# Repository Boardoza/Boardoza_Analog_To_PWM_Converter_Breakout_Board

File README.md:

# Boardoza Analog To PWM Converter Breakout Board

The **Boardoza Analog to PWM Converter Breakout Board** is a high-precision signal conditioning board designed to convert an analog voltage input into a proportional **PWM (Pulse Width Modulation)** output signal where the **duty cycle increases or decreases proportionally with the applied input voltage**. Built using high-speed operational amplifiers and comparators, this board operates entirely through dedicated hardware circuitry, enabling ultra-fast response times and reliable signal conversion without requiring any firmware or software processing.

This breakout board is ideal for **motor control systems, throttle signal conversion, industrial automation, power electronics, robotics, and embedded analog control applications**. Its low-latency architecture and robust analog signal path make it suitable for safety-critical and noise-sensitive environments where deterministic signal behavior is essential.

## [Click here to purchase!](https://www.ozdisan.com/ureticiler/boardoza)

|Front Side|Back Side|
|:---:|:---:|
| | |

---

## Key Features

- **Hardware-Based PWM Generation:** Converts analog voltage signals directly into PWM output without requiring a microcontroller.
- **Discrete Analog Design:** Built using precision operational amplifiers and comparators for stable and deterministic operation.
- **Low Latency Signal Path:** Near-instantaneous analog-to-PWM conversion suitable for real-time control systems.
- **Push-Pull CMOS Output:** Provides strong and clean logic-level PWM output compatible with many digital systems.
- **High Noise Immunity:** Reliable operation in electrically noisy environments such as motor drivers and industrial systems.

---

## Technical Specifications

**Model:** Analog to PWM Converter  
**Manufacturer:** Boardoza   
**Manufacturer IC:** Texas Instruments   
**Operational Amplifier Model:** OPA2356  
**Board Type:** Analog Signal Converter    
**Input Voltage (VCC):** 2.7V – 5.5V  
**Analog Input Range:** 0.1V – 4.9V  
**Output Type:** 20kHz PWM (Push-Pull CMOS Logic)  
**Comparator Type:** High-Speed Comparator with Integrated Reference  
**Operational Amplifier Type:** Rail-to-Rail High-Speed Op-Amp  
**Output Short Circuit Current:** 74mA  
**Operating Temperature:** -40°C to +125°C  
**Board Dimensions:** 40mm x 20mm  v

---

## Simulation and Test Results

Simulation and test results are provided below.

| Triangle Wave Output | Error Amplifier Output | PWM Output |
|:---:|:---:|:---:|
|  |  |  |

| Input 100mV | Input 3.3V |
|:---:|:---:|
|  |  |

---

## Board Pinout

### ( J1 ) Power & Analog Input Connector

| Pin Number | Pin Name | Description |
|:---:|:---:|---|
| 1 | VCC | Power Supply Input |
| 2 | INPUT | Analog Voltage Input / Throttle Signal |
| 3 | GND | Ground |

### ( J2 ) PWM Output Connector

| Pin Number | Pin Name | Description |
|:---:|:---:|---|
| 1 | VCC | Power Supply Input |
| 2 | GND | Ground |

---

## Board Dimensions

---

## Step Files

[Boardoza ANALOG to PWM Converter.step](./assets/ANALOG_To_PWM_Converter%20Step.step)

---

## Datasheet

[OPA2356 Datasheet.pdf](./assets/OPA2356xxD%20Datasheet.pdf)

[TLV3052 Datasheet.pdf](./assets/TLV3052AID%20Datasheet.pdf)

---

## Version History

- V1.0.0 - Initial Release

---

## Support

- If you have any questions or need support, please contact support@boardoza.com

---

## **License**
### **Hardware Design**

[![CC BY-SA 4.0][cc-by-sa-shield]][cc-by-sa]

All hardware design files are licensed under [Creative Commons Attribution-ShareAlike 4.0 International License][cc-by-sa].

[cc-by-sa]: http://creativecommons.org/licenses/by-sa/4.0/
[cc-by-sa-shield]: https://img.shields.io/badge/License-CC%20BY--SA%204.0-lightgrey.svg

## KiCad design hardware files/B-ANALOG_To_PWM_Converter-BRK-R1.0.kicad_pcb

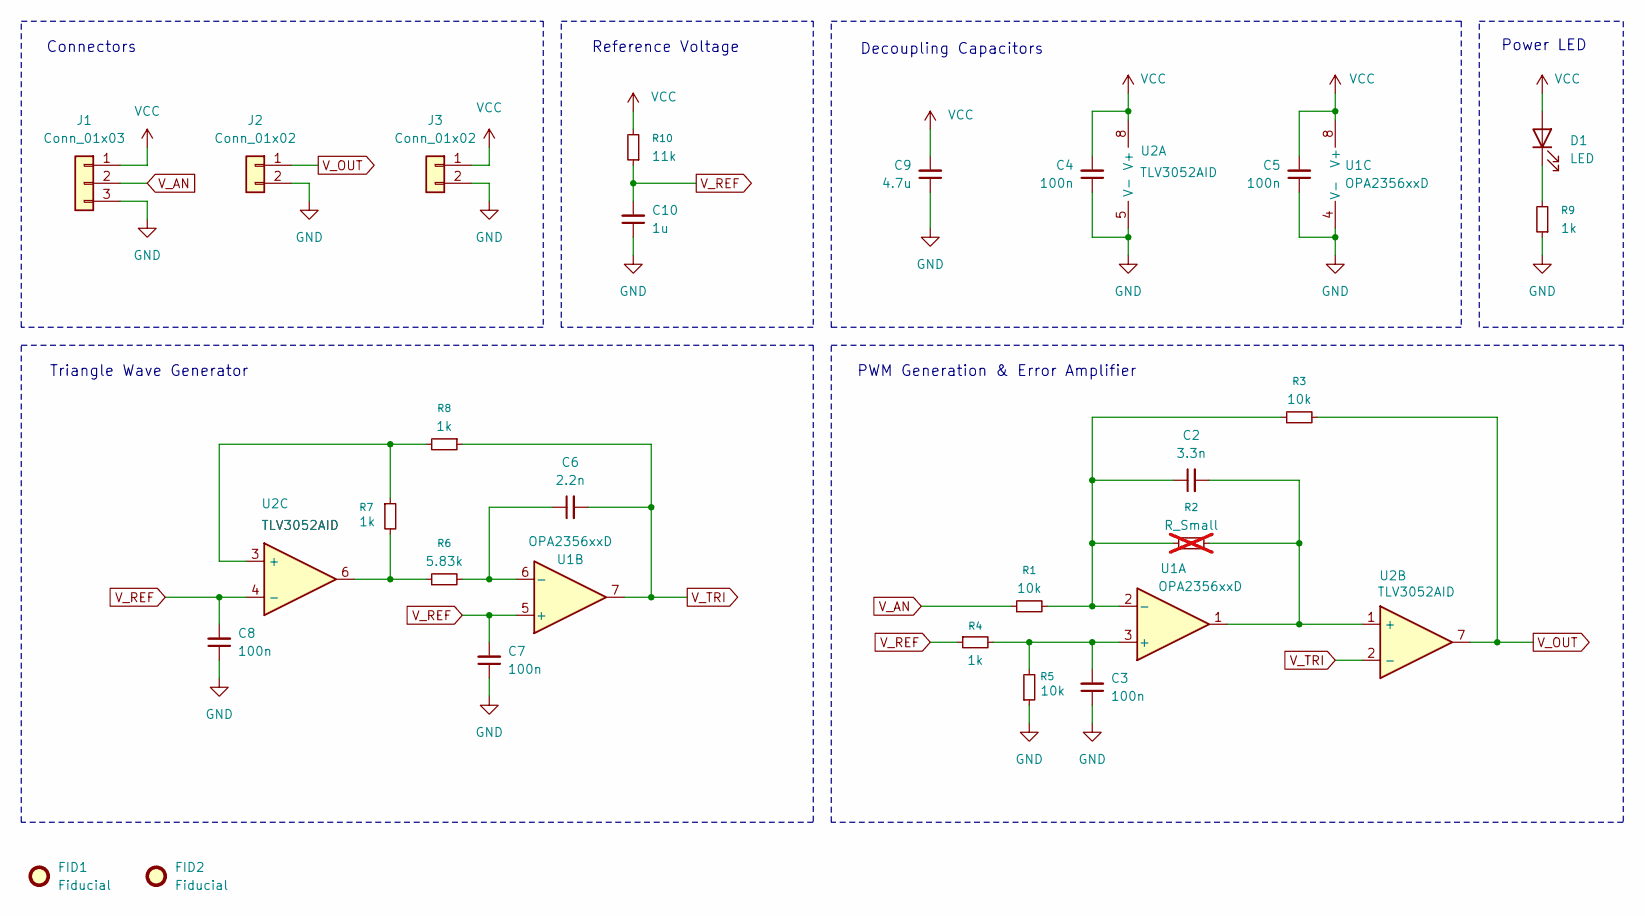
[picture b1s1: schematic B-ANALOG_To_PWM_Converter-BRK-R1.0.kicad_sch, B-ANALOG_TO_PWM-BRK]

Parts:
C2: 3.3n; C_0603_1608Metric; MPN CL10C332JA8NNNC
C3, C4, C5, C7, C8: 100n; C_0603_1608Metric; MPN CC0603KRX7R9BB104
C6: 2.2n; C_0603_1608Metric; MPN CL10C222JB8NNNC
C9: 4.7u; C_0603_1608Metric; MPN CL10A475KP8NNNC
C10: 1u; C_0603_1608Metric; MPN CL10B105KO8NNNC
D1: LED; LED_0603_1608Metric; MPN LTST-C190KRKT
FID1, FID2: Fiducial; Fiducial_0.5mm_Mask1mm
J1: Conn_01x03; JST_XH_B3B-XH-A_1x03_P2.50mm_Vertical; MPN L-KLS1-2.50-03-SB
J2, J3: Conn_01x02; JST_XH_B2B-XH-A_1x02_P2.50mm_Vertical; MPN L-KLS1-2.50-02-SB
R1, R3, R5: 10k; R_0603_1608Metric; MPN TC0350B1002T5F
R2: R_Small; R_0603_1608Metric; not fitted
R4, R7, R8, R9: 1k; R_0603_1608Metric; MPN TC0325D1001T5C
R6: 5.83k; R_0603_1608Metric; MPN RN73R1JTTD5831B25
R10: 11k; R_0603_1608Metric; MPN ERJPB3B1102V
U1: OPA2356xxD; SOIC-8_5.3x6.2mm_P1.27mm; MPN OPA2356AID
U2: TLV3052AID; SOIC-8_5.3x6.2mm_P1.27mm; MPN TLV3502AID

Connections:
GND: C3.1, C4.1, C5.1, C7.1, C8.1, C9.1, C10.1, J1.3, J2.2, J3.2, R5.1, R9.1, U1.4 (V-), U2.5 (V-)
unnamed: D1.1 (K), R9.2
unnamed: R6.1, R7.2, U2.6
unnamed: C3.2, R4.2, R5.2, U1.3 (+)
unnamed: C2.1, R1.2, R2.1, R3.1, U1.2 (-)
unnamed: C6.1, R6.2, U1.6 (-)
unnamed: C2.2, R2.2, U1.1, U2.1 (+)
unnamed: R7.1, R8.2, U2.3 (+)
VCC: C4.2, C5.2, C9.2, D1.2 (A), J1.1, J3.1, R10.2, U1.8 (V+), U2.8 (V+)
V_AN: J1.2, R1.1
V_OUT: J2.1, R3.2, U2.7
V_REF: C7.2, C8.2, C10.2, R4.1, R10.1, U1.5 (+), U2.4 (-)
V_TRI: C6.2, R8.1, U1.7, U2.2 (-)

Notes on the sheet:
Connectors
Triangle Wave Generator
Power LED
Reference Voltage
Decoupling Capacitors
PWM Generation & Error Amplifier

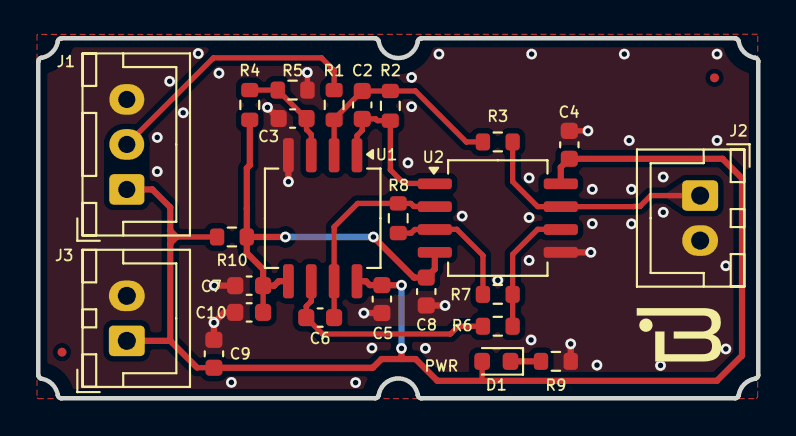
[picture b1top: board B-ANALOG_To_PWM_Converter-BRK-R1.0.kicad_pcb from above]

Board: 2 copper layers, 40.0 x 20.0 mm, 27 parts (0 on the bottom side), 13 nets.
